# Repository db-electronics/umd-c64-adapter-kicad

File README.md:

# Copyright and Disclaimer
Copyright: René Richard

This documentation describes Open Hardware and is licensed under the
CERN OHL v. 1.2.

You may redistribute and modify this documentation under the terms of the
CERN OHL v.1.2. (http://ohwr.org/cernohl). This documentation is distributed
WITHOUT ANY EXPRESS OR IMPLIED WARRANTY, INCLUDING OF
MERCHANTABILITY, SATISFACTORY QUALITY AND FITNESS FOR A
PARTICULAR PURPOSE. Please see the CERN OHL v.1.2 for applicable
conditions

# C64 UMD Adapter
This KiCad project contains the Commodore 64 cartridge adapter for the [Universal Mega Dumper](https://github.com/db-electronics/Universal-Mega-Dumper).

## ID
* 0x02

Each UMD adapter contains a serial shift register with an 8bit ID.

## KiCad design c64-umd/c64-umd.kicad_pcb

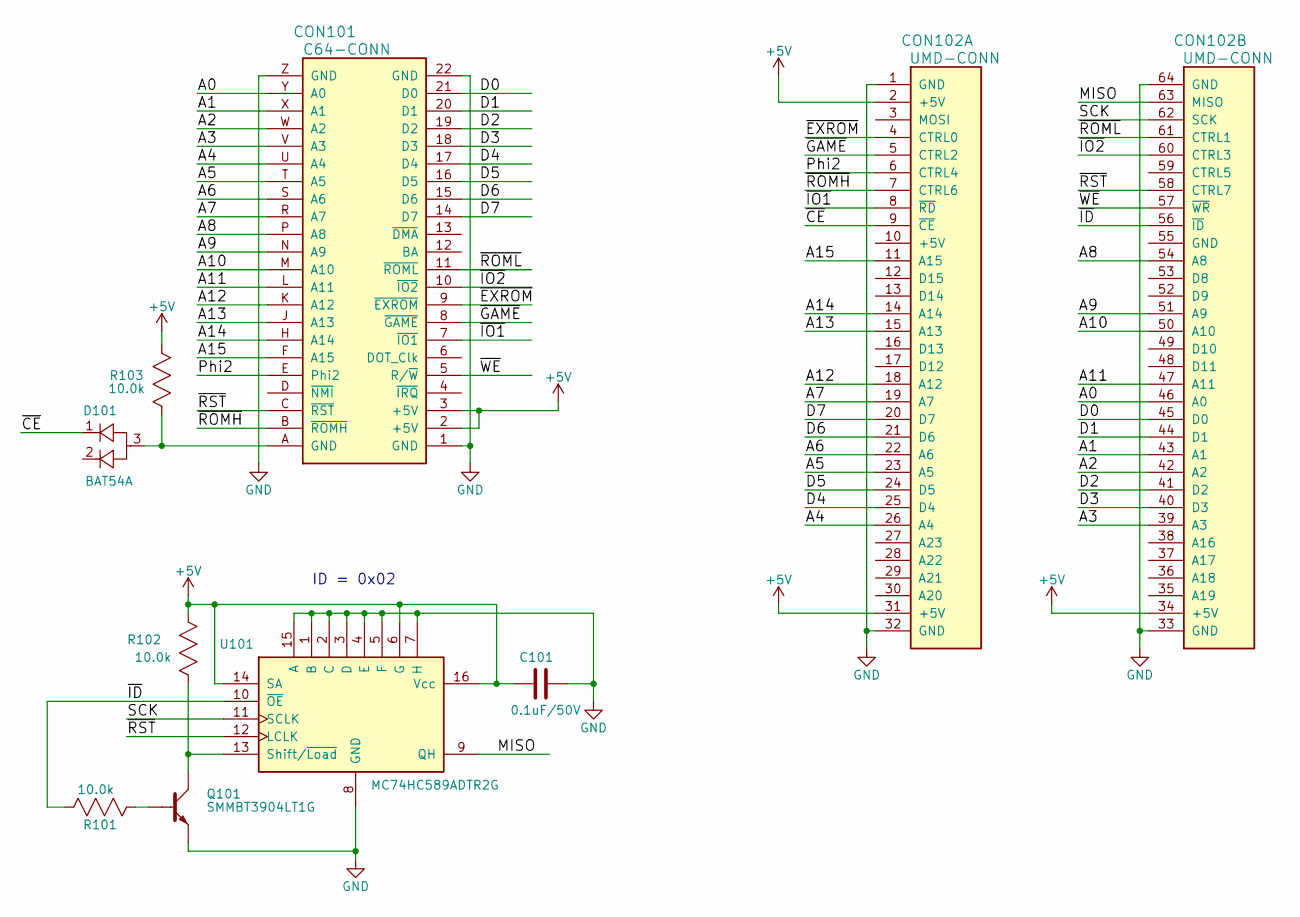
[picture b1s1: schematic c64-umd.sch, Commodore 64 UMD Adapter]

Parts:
C101: 0.1uF/50V; 0603; Digikey 445-5666-1-ND
CON101: C64-CONN; Digikey #ND
CON102: UMD-CONN; UMD-CONN-DIP64
D101: BAT54A; SOT23; Digikey BAT54AFSCT-ND
Q101: SMMBT3904LT1G; SOT23; Digikey SMMBT3904LT1GOSCT-ND
R101, R102, R103: 10.0k; 0603; Digikey P10.0KHCT-ND
U101: MC74HC589ADTR2G; TSSOP-16; Digikey MC74HC589ADTR2GOSCT-ND

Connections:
+5V: C101.2, CON101.2 (+5V), CON101.3 (+5V), CON102.2 (+5V), CON102.31 (+5V), CON102.34 (+5V), R102.1, R103.1, U101.6 (G), U101.14 (SA), U101.16 (Vcc)
/A0: CON101.Y (A0), CON102.46 (A0)
/A1: CON101.X (A1), CON102.43 (A1)
/A2: CON101.W (A2), CON102.42 (A2)
/A3: CON101.V (A3), CON102.39 (A3)
/A4: CON101.U (A4), CON102.26 (A4)
/A5: CON101.T (A5), CON102.23 (A5)
/A6: CON101.S (A6), CON102.22 (A6)
/A7: CON101.R (A7), CON102.19 (A7)
/A8: CON101.P (A8), CON102.54 (A8)
/A9: CON101.N (A9), CON102.51 (A9)
/A10: CON101.M (A10), CON102.50 (A10)
/A11: CON101.L (A11), CON102.47 (A11)
/A12: CON101.K (A12), CON102.18 (A12)
/A13: CON101.J (A13), CON102.15 (A13)
/A14: CON101.H (A14), CON102.14 (A14)
/A15: CON101.F (A15), CON102.11 (A15)
/D0: CON101.21 (D0), CON102.45 (D0)
/D1: CON101.20 (D1), CON102.44 (D1)
/D2: CON101.19 (D2), CON102.41 (D2)
/D3: CON101.18 (D3), CON102.40 (D3)
/D4: CON101.17 (D4), CON102.25 (D4)
/D5: CON101.16 (D5), CON102.24 (D5)
/D6: CON101.15 (D6), CON102.21 (D6)
/D7: CON101.14 (D7), CON102.20 (D7)
/MISO: CON102.63 (MISO), U101.9 (QH)
/Phi2: CON101.E (Phi2), CON102.6 (CTRL4)
/SCK: CON102.62 (SCK), U101.11 (SCLK)
/~CE: CON102.9 (~CE), D101.1
/~EXROM: CON101.9 (~EXROM), CON102.4 (CTRL0)
/~GAME: CON101.8 (~GAME), CON102.5 (CTRL2)
/~ID: CON102.56 (~ID), R101.2, U101.10 (~OE)
/~IO1: CON101.7 (~IO1), CON102.8 (~RD)
/~IO2: CON101.10 (~IO2), CON102.60 (CTRL3)
/~ROMH: CON101.B (~ROMH), CON102.7 (CTRL6)
/~ROML: CON101.11 (~ROML), CON102.61 (CTRL1)
/~RST: CON101.C (~RST), CON102.58 (CTRL7), U101.12 (LCLK)
/~WE: CON101.5 (R/~W), CON102.57 (~WR)
GND: C101.1, CON101.1 (GND), CON101.22 (GND), CON101.Z (GND), CON102.1 (GND), CON102.32 (GND), CON102.33 (GND), CON102.64 (GND), Q101.2 (E), U101.1 (B), U101.2 (C), U101.3 (D), U101.4 (E), U101.5 (F), U101.7 (H), U101.8 (GND), U101.15 (A)
unnamed: CON101.A (GND), D101.3, R103.2
unnamed: Q101.1 (B), R101.1
unnamed: Q101.3 (C), R102.2, U101.13 (Shift/~Load)

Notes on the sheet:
ID = 0x02

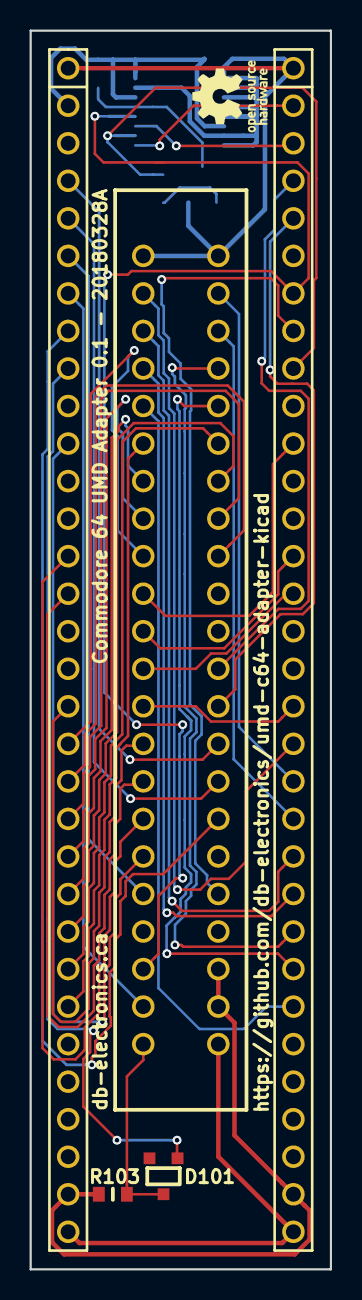
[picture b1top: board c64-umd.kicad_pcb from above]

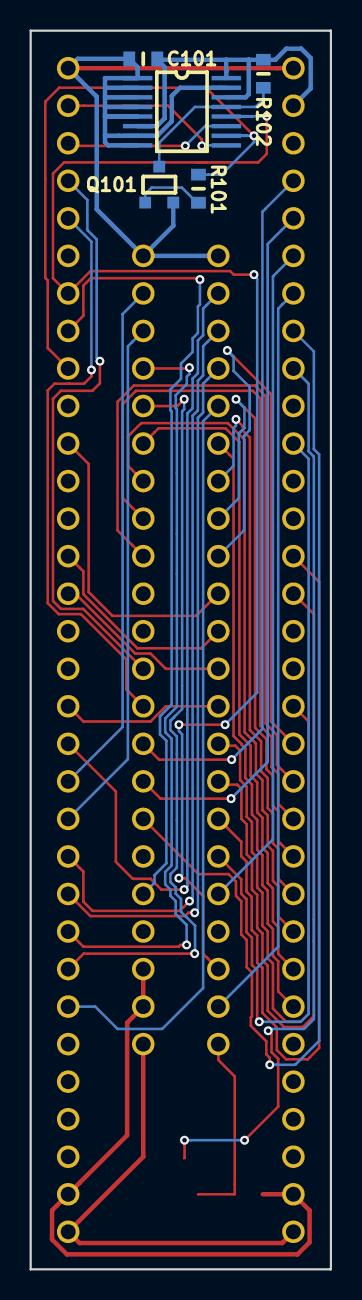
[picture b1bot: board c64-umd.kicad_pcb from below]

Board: 2 copper layers, 20.3 x 83.8 mm, 9 parts (5 on the bottom side), 42 nets.

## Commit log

2018-03-28 added license info
2018-03-28 prelim sch done
2018-03-29 pcb outline and parts layout
2018-03-29 prelim routing complete, review before 0.1 release
2018-04-04 generated 0.1 gerbers
